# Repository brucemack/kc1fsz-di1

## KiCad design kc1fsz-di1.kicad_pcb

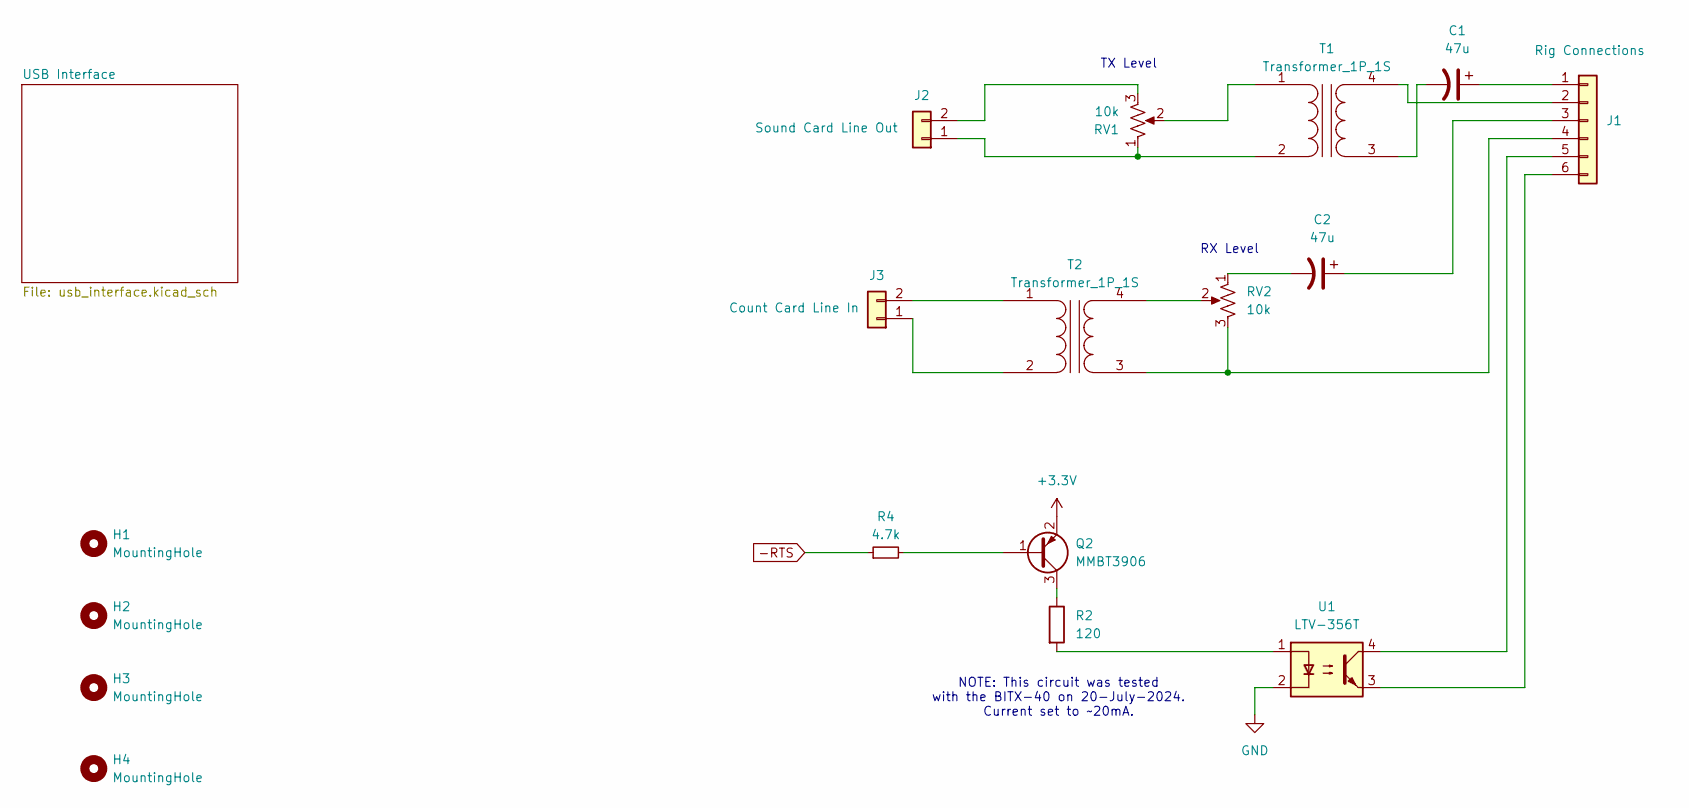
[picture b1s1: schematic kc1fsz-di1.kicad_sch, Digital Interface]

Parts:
C1, C2: 47u; CP_Radial_D5.0mm_P2.50mm
H1, H2, H3, H4: MountingHole; MountingHole_4mm
J1: Rig Connections; PinHeader_1x06_P2.54mm_Vertical
J2: Sound Card Line Out; PinHeader_1x02_P2.54mm_Vertical
J3: Count Card Line In; PinHeader_1x02_P2.54mm_Vertical
Q2: MMBT3906; SOT-23
R2: 120; R_0805_2012Metric_Pad1.20x1.40mm_HandSolder
R4: 4.7k; R_0805_2012Metric_Pad1.20x1.40mm_HandSolder
RV1, RV2: 10k; POT_3362P
T1, T2: Transformer_1P_1S; CheapAudioTransformer
U1: LTV-356T; SO-4_4.4x3.6mm_P2.54mm

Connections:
+3.3V: Q2.2 (E); also elsewhere on the board
-RTS: R4.1; also elsewhere on the board
GND: U1.2; also elsewhere on the board
unnamed: C2.2, RV2.1
unnamed: C1.1, J1.1
unnamed: J1.2, T1.4 (SB)
unnamed: C2.1, J1.3
unnamed: J1.4, RV2.3, T2.3 (SA)
unnamed: J1.5, U1.4
unnamed: J1.6, U1.3
unnamed: J2.1, RV1.1, T1.2 (AB)
unnamed: J2.2, RV1.3
unnamed: J3.1, T2.2 (AB)
unnamed: J3.2, T2.1 (AA)
unnamed: Q2.1 (B), R4.2
unnamed: Q2.3 (C), R2.1
unnamed: R2.2, U1.1
unnamed: RV1.2, T1.1 (AA)
unnamed: C1.2, T1.3 (SA)
unnamed: RV2.2, T2.4 (SB)

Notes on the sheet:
RX Level
NOTE: This circuit was tested with the BITX-40 on 20-July-2024. Current set to ~20mA.
TX Level

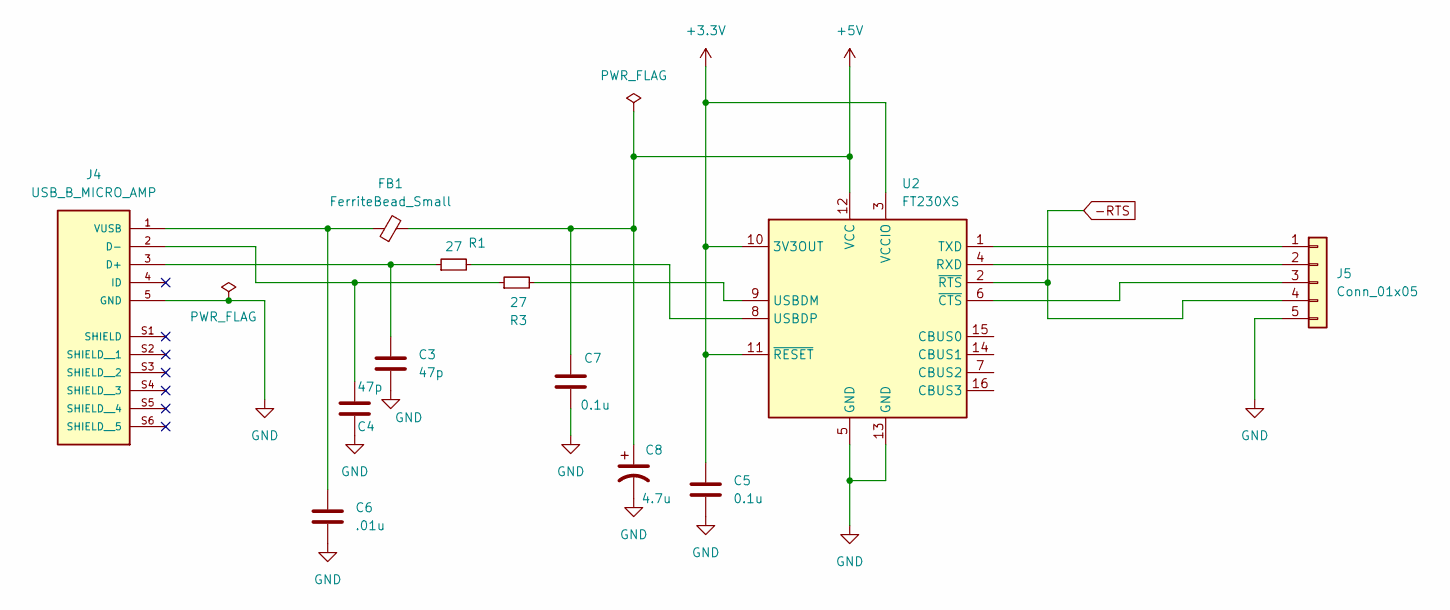
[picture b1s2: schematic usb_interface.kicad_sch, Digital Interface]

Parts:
C3, C4: 47p; C_0805_2012Metric_Pad1.18x1.45mm_HandSolder
C5, C7: 0.1u; C_0805_2012Metric_Pad1.18x1.45mm_HandSolder
C6: .01u; C_0805_2012Metric_Pad1.18x1.45mm_HandSolder
C8: 4.7u; CP_Radial_D5.0mm_P2.50mm
FB1: FerriteBead_Small; L_0805_2012Metric_Pad1.15x1.40mm_HandSolder
J4: USB_B_MICRO_AMP; AMPHENOL_10118193-0001LF; PARTREV E
J5: Conn_01x05; PinHeader_1x05_P2.54mm_Vertical
R1, R3: 27; R_0805_2012Metric_Pad1.20x1.40mm_HandSolder
U2: FT230XS; SSOP-16_3.9x4.9mm_P0.635mm

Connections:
+3.3V: C5.1, U2.3 (VCCIO), U2.10 (3V3OUT), U2.11 (~RESET); also elsewhere on the board
+5V: C7.1, C8.1, FB1.2, U2.12 (VCC)
-RTS: J5.4, U2.2 (~RTS); also elsewhere on the board
GND: C3.2, C4.2, C5.2, C6.2, C7.2, C8.2, J4.5 (GND), J5.5, U2.5 (GND), U2.13 (GND); also elsewhere on the board
unnamed: C3.1, J4.3 (D+), R1.1
unnamed: C4.1, J4.2 (D-), R3.1
unnamed: C6.1, FB1.1, J4.1 (VUSB)
unnamed: J5.1, U2.1 (TXD)
unnamed: J5.2, U2.4 (RXD)
unnamed: J5.3, U2.6 (~CTS)
unnamed: R3.2, U2.9 (USBDM)
unnamed: R1.2, U2.8 (USBDP)

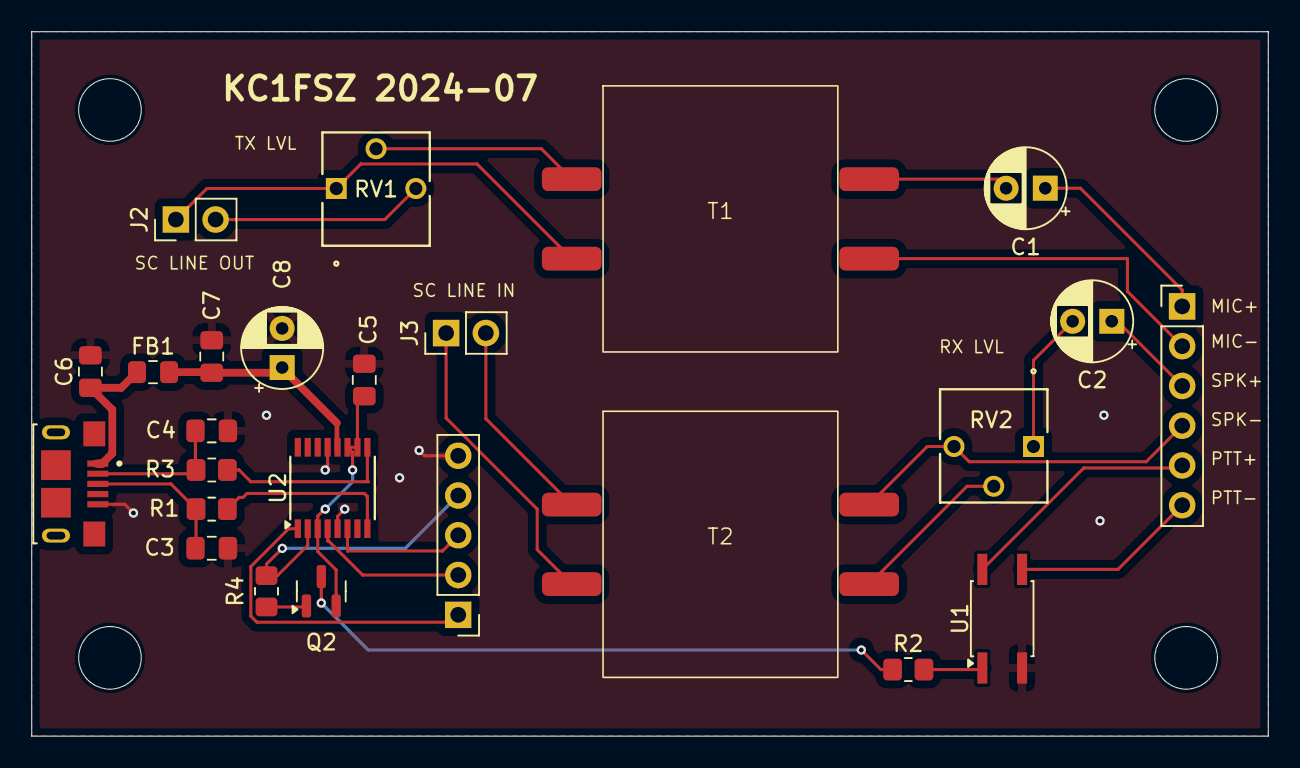
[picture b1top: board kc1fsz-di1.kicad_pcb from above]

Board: 2 copper layers, 79.0 x 45.0 mm, 29 parts (0 on the bottom side), 29 nets.
